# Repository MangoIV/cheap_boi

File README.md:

# The cheap_boi mechanical keyboard
### The cheap_boi is going to be a new custom mechanical keyboard with a low pricetag
## TL;DR
- WIP, PCB v0.2 has been tested and confirmed working 
- cheap, ortholinear keyboard with  OLED-Display and RGB underglow
- Gerbers added, print on own risk
- [BOM](http://htmlpreview.github.io/?https://github.com/MangoIV/cheap_boi/bom/ibom.html)
## Render of front side

## Features
### implemented
- microcontroller ATmega32u4
- ortholinear layout similar to the planck
- 4 individual function keys 
- underglow LEDs using WS2812B
- OLED display using SSD1306
- FR4 Bottom- and Switchplate with windows to see microcontroller and OLED
- have a look at the folder "renders" to see renders of the PCB and plates
- a working firmware exists on my fork of the qmk_firmware on the branch cheap_boi
- acrylic case has been made and is confirmed working 
- easier crystal footprint since v0.2
### planned
- alps/mx hybrid switch cutouts on the top plate
- add some nice silkscreen art on PCB and top plate 
### in the future
- change the design to arm, won't come that quickly though 
### current status concerning prototype
- PCBs and parts have arrived and been tested
- the second Prototype has been built and is fully working 
### problems of the current design
- the fit of the acrylic top plate wit the oled is very tight. this results in the need of filing of some materials off the corner of the oleds, this isn't much work tho and doesn't change the functionality of the oled

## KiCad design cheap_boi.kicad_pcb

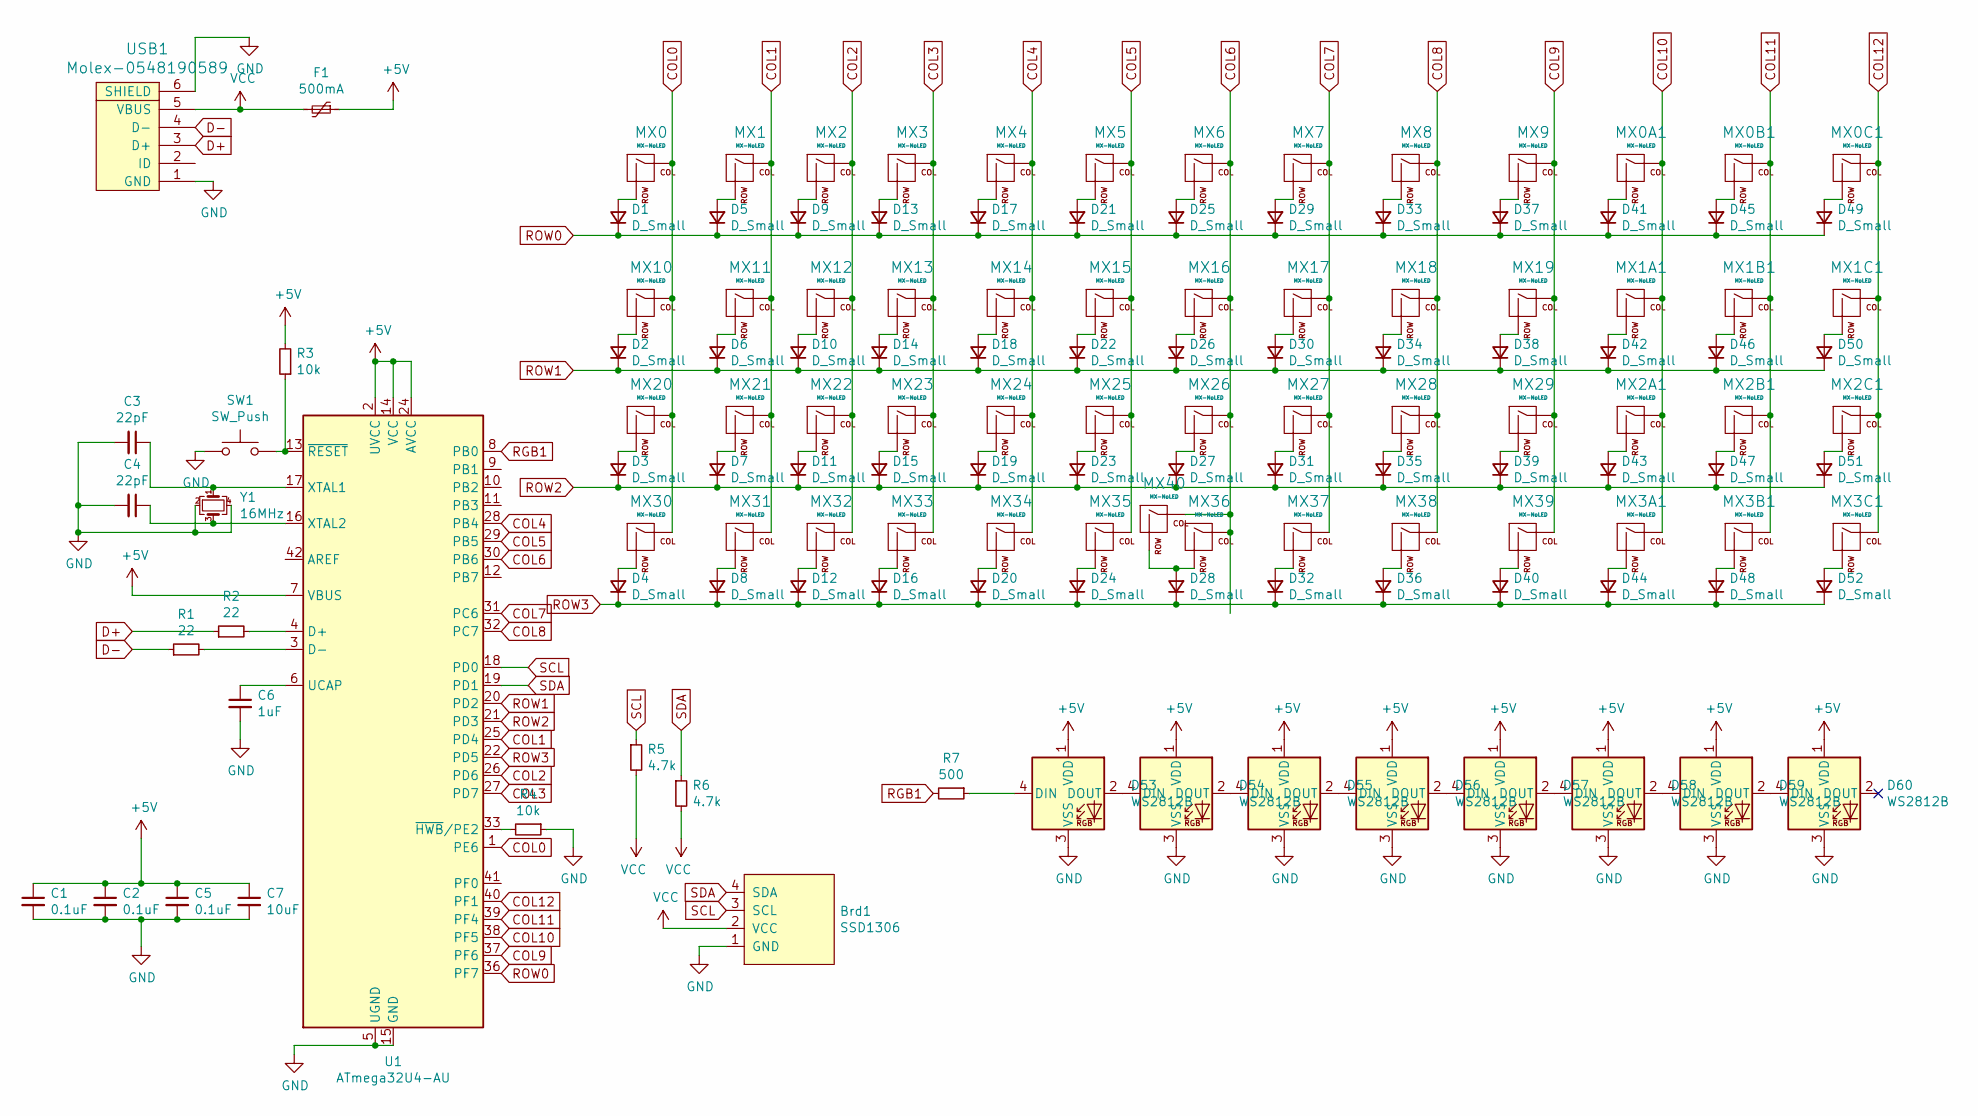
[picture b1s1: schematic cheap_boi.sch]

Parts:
Brd1: SSD1306; 128x64OLED
C1, C2, C5: 0.1uF; C_0805_2012Metric
C3, C4: 22pF; C_0805_2012Metric
C6: 1uF; C_0805_2012Metric
C7: 10uF; C_0805_2012Metric
D1, D2, D3, D4, D5, D6, D7, D8, D9, D10, D11, D12, D13, D14, D15, D16, D17, D18, D19, D20, D21, D22, D23, D24, D25, D26, D27, D28, D29, D30, D31, D32, D33, D34, D35, D36, D37, D38, D39, D40, D41, D42, D43, D44, D45, D46, D47, D48, D49, D50, D51, D52: D_Small; D_SOD-123
D53, D54, D55, D56, D57, D58, D59, D60: WS2812B; LED_WS2812B_PLCC4_5.0x5.0mm_P3.2mm
F1: 500mA; Fuse_1206_3216Metric
MX0, MX0A1, MX0B1, MX0C1, MX1, MX1A1, MX1B1, MX1C1, MX2, MX2A1, MX2B1, MX2C1, MX3, MX3A1, MX3B1, MX3C1, MX4, MX5, MX6, MX7, MX8, MX9, MX10, MX11, MX12, MX13, MX14, MX15, MX16, MX17, MX18, MX19, MX20, MX21, MX22, MX23, MX24, MX25, MX26, MX27, MX28, MX29, MX30, MX31, MX32, MX33, MX34, MX35, MX36, MX37, MX38, MX39: MX-NoLED; MX-1U-NoLED
MX40: MX-NoLED; MX-2U-ReversedStabilizers-NoLED
R1, R2: 22; R_0805_2012Metric
R3, R4: 10k; R_0805_2012Metric
R5, R6: 4.7k; R_0805_2012Metric
R7: 500; R_0805_2012Metric
SW1: SW_Push; SKQG-1155865
U1: ATmega32U4-AU; TQFP-44_10x10mm_P0.8mm
USB1: Molex-0548190589
Y1: 16MHz; Crystal_SMD_3225-4Pin_3.2x2.5mm_HandSoldering

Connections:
+5V: C1.1, C2.1, C5.1, C7.1, D53.1 (VDD), D54.1 (VDD), D55.1 (VDD), D56.1 (VDD), D57.1 (VDD), D58.1 (VDD), D59.1 (VDD), D60.1 (VDD), F1.1, R3.2, U1.2 (UVCC), U1.7 (VBUS), U1.14 (VCC), U1.24 (AVCC), U1.34 (VCC), U1.44 (AVCC)
COL0: MX0.1 (COL), MX10.1 (COL), MX20.1 (COL), MX30.1 (COL), U1.1 (PE6)
COL1: MX1.1 (COL), MX11.1 (COL), MX21.1 (COL), MX31.1 (COL), U1.25 (PD4)
COL2: MX2.1 (COL), MX12.1 (COL), MX22.1 (COL), MX32.1 (COL), U1.26 (PD6)
COL3: MX3.1 (COL), MX13.1 (COL), MX23.1 (COL), MX33.1 (COL), U1.27 (PD7)
COL4: MX4.1 (COL), MX14.1 (COL), MX24.1 (COL), MX34.1 (COL), U1.28 (PB4)
COL5: MX5.1 (COL), MX15.1 (COL), MX25.1 (COL), MX35.1 (COL), U1.29 (PB5)
COL6: MX6.1 (COL), MX16.1 (COL), MX26.1 (COL), MX36.1 (COL), MX40.1 (COL), U1.30 (PB6)
COL7: MX7.1 (COL), MX17.1 (COL), MX27.1 (COL), MX37.1 (COL), U1.31 (PC6)
COL8: MX8.1 (COL), MX18.1 (COL), MX28.1 (COL), MX38.1 (COL), U1.32 (PC7)
COL9: MX9.1 (COL), MX19.1 (COL), MX29.1 (COL), MX39.1 (COL), U1.37 (PF6)
COL10: MX0A1.1 (COL), MX1A1.1 (COL), MX2A1.1 (COL), MX3A1.1 (COL), U1.38 (PF5)
COL11: MX0B1.1 (COL), MX1B1.1 (COL), MX2B1.1 (COL), MX3B1.1 (COL), U1.39 (PF4)
COL12: MX0C1.1 (COL), MX1C1.1 (COL), MX2C1.1 (COL), MX3C1.1 (COL), U1.40 (PF1)
D+: R2.1, USB1.3 (D+)
D-: R1.1, USB1.4 (D-)
GND: Brd1.1 (GND), C1.2, C2.2, C3.2, C4.2, C5.2, C6.2, C7.2, D53.3 (VSS), D54.3 (VSS), D55.3 (VSS), D56.3 (VSS), D57.3 (VSS), D58.3 (VSS), D59.3 (VSS), D60.3 (VSS), R4.1, SW1.1, U1.5 (UGND), U1.15 (GND), U1.23 (GND), U1.35 (GND), U1.43 (GND), USB1.1 (GND), USB1.6 (SHIELD), Y1.2, Y1.4
unnamed: C3.1, U1.17 (XTAL1), Y1.1
unnamed: C4.1, U1.16 (XTAL2), Y1.3
unnamed: C6.1, U1.6 (UCAP)
unnamed: D1.2 (A), MX0.2 (ROW)
unnamed: D2.2 (A), MX10.2 (ROW)
unnamed: D3.2 (A), MX20.2 (ROW)
unnamed: D4.2 (A), MX30.2 (ROW)
unnamed: D5.2 (A), MX1.2 (ROW)
unnamed: D6.2 (A), MX11.2 (ROW)
unnamed: D7.2 (A), MX21.2 (ROW)
unnamed: D8.2 (A), MX31.2 (ROW)
unnamed: D9.2 (A), MX2.2 (ROW)
unnamed: D10.2 (A), MX12.2 (ROW)
unnamed: D11.2 (A), MX22.2 (ROW)
unnamed: D12.2 (A), MX32.2 (ROW)
unnamed: D13.2 (A), MX3.2 (ROW)
unnamed: D14.2 (A), MX13.2 (ROW)
unnamed: D15.2 (A), MX23.2 (ROW)
unnamed: D16.2 (A), MX33.2 (ROW)
unnamed: D17.2 (A), MX4.2 (ROW)
unnamed: D18.2 (A), MX14.2 (ROW)
unnamed: D19.2 (A), MX24.2 (ROW)
unnamed: D20.2 (A), MX34.2 (ROW)
unnamed: D21.2 (A), MX5.2 (ROW)
unnamed: D22.2 (A), MX15.2 (ROW)
unnamed: D23.2 (A), MX25.2 (ROW)
unnamed: D24.2 (A), MX35.2 (ROW)
unnamed: D25.2 (A), MX6.2 (ROW)
unnamed: D26.2 (A), MX16.2 (ROW)
unnamed: D27.2 (A), MX26.2 (ROW)
unnamed: D28.2 (A), MX36.2 (ROW), MX40.2 (ROW)
unnamed: D29.2 (A), MX7.2 (ROW)
unnamed: D30.2 (A), MX17.2 (ROW)
unnamed: D31.2 (A), MX27.2 (ROW)
unnamed: D32.2 (A), MX37.2 (ROW)
unnamed: D33.2 (A), MX8.2 (ROW)
unnamed: D34.2 (A), MX18.2 (ROW)
unnamed: D35.2 (A), MX28.2 (ROW)
unnamed: D36.2 (A), MX38.2 (ROW)
unnamed: D37.2 (A), MX9.2 (ROW)
unnamed: D38.2 (A), MX19.2 (ROW)
unnamed: D39.2 (A), MX29.2 (ROW)
unnamed: D40.2 (A), MX39.2 (ROW)
unnamed: D41.2 (A), MX0A1.2 (ROW)
unnamed: D42.2 (A), MX1A1.2 (ROW)
unnamed: D43.2 (A), MX2A1.2 (ROW)
unnamed: D44.2 (A), MX3A1.2 (ROW)
unnamed: D45.2 (A), MX0B1.2 (ROW)
unnamed: D46.2 (A), MX1B1.2 (ROW)
unnamed: D47.2 (A), MX2B1.2 (ROW)
unnamed: D48.2 (A), MX3B1.2 (ROW)
unnamed: D49.2 (A), MX0C1.2 (ROW)
unnamed: D50.2 (A), MX1C1.2 (ROW)
unnamed: D51.2 (A), MX2C1.2 (ROW)
unnamed: D52.2 (A), MX3C1.2 (ROW)
unnamed: D53.2 (DOUT), D54.4 (DIN)
unnamed: D53.4 (DIN), R7.1
unnamed: D54.2 (DOUT), D55.4 (DIN)
unnamed: D55.2 (DOUT), D56.4 (DIN)
unnamed: D56.2 (DOUT), D57.4 (DIN)
unnamed: D57.2 (DOUT), D58.4 (DIN)
unnamed: D58.2 (DOUT), D59.4 (DIN)
unnamed: D59.2 (DOUT), D60.4 (DIN)
unnamed: R1.2, U1.3 (D-)
unnamed: R2.2, U1.4 (D+)
unnamed: R3.1, SW1.2, U1.13 (~RESET)
unnamed: R4.2, U1.33 (~HWB~/PE2)
RGB1: R7.2, U1.8 (PB0)
ROW0: D1.1 (K), D5.1 (K), D9.1 (K), D13.1 (K), D17.1 (K), D21.1 (K), D25.1 (K), D29.1 (K), D33.1 (K), D37.1 (K), D41.1 (K), D45.1 (K), D49.1 (K), U1.36 (PF7)
ROW1: D2.1 (K), D6.1 (K), D10.1 (K), D14.1 (K), D18.1 (K), D22.1 (K), D26.1 (K), D30.1 (K), D34.1 (K), D38.1 (K), D42.1 (K), D46.1 (K), D50.1 (K), U1.20 (PD2)
ROW2: D3.1 (K), D7.1 (K), D11.1 (K), D15.1 (K), D19.1 (K), D23.1 (K), D27.1 (K), D31.1 (K), D35.1 (K), D39.1 (K), D43.1 (K), D47.1 (K), D51.1 (K), U1.21 (PD3)
ROW3: D4.1 (K), D8.1 (K), D12.1 (K), D16.1 (K), D20.1 (K), D24.1 (K), D28.1 (K), D32.1 (K), D36.1 (K), D40.1 (K), D44.1 (K), D48.1 (K), D52.1 (K), U1.22 (PD5)
SCL: Brd1.3 (SCL), R5.1, U1.18 (PD0)
SDA: Brd1.4 (SDA), R6.1, U1.19 (PD1)
VCC: Brd1.2 (VCC), F1.2, R5.2, R6.2, USB1.5 (VBUS)

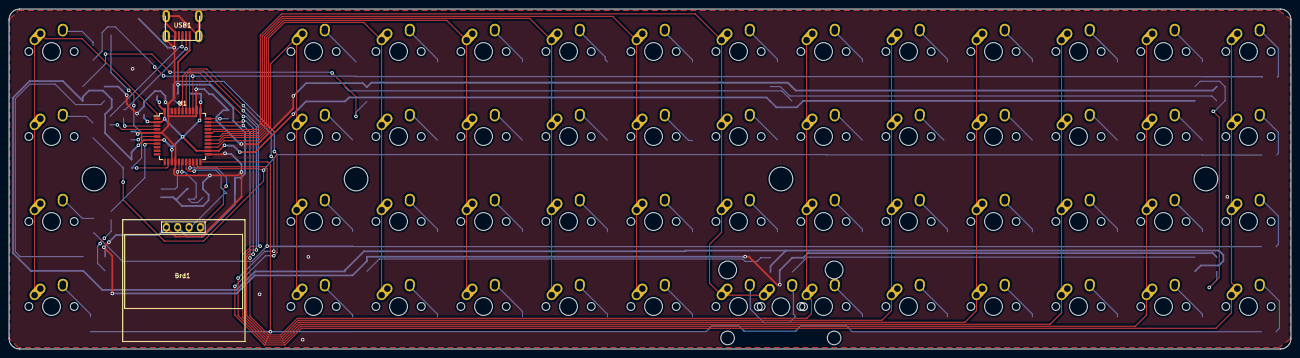
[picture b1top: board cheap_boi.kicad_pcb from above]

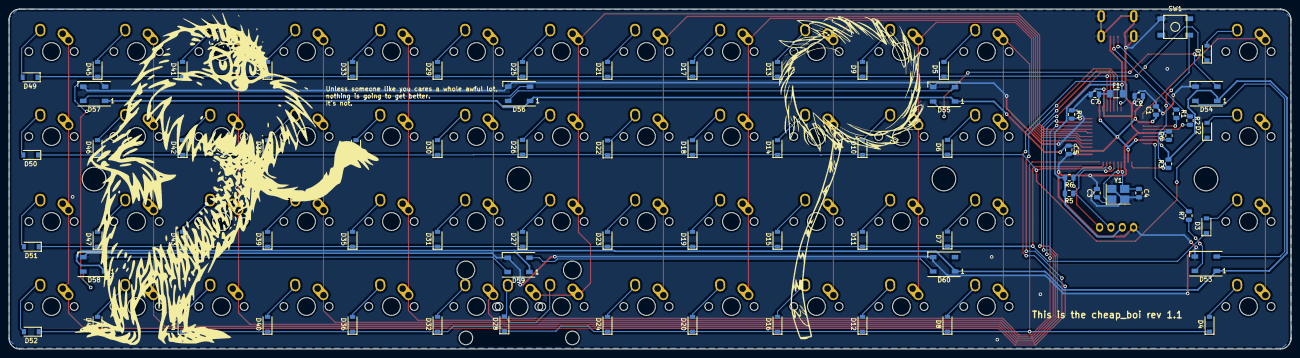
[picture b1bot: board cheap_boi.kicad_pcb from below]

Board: 2 copper layers, 287.3 x 76.2 mm, 137 parts (77 on the bottom side), 92 nets.

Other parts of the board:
 : MountingHole_5.3mm_M5
 #2,  #3,  #4: MountingHole_5.3mm_M5

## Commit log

2020-06-20 create kicad project
2020-06-20 add submodules
2020-06-20 update footprints
2020-06-20 added schematic
2020-06-20 assigned footprints for all components
2020-06-20 sorted and ordered most of the components
2020-06-20 everything added besides cutout and usb-connector
2020-06-20 last commit of the day
2020-06-21 add SSD1306-128x64 submodule
2020-06-21 added RGB breakout and ordered parts in symmetrically
2020-06-21 added connection of rows and cols to microcontroller
2020-06-21 tracing is done, PCB should be functional
2020-06-22 silkscreen text, GND fill, error checking
2020-06-22 added RGB underglow, removed 3 pin breakout for RGB underglow
2020-06-22 add png render front side of pcb
2020-06-22 change file name, merge
2020-06-22 u see what i did
2020-06-22 added evenly distributed groundfill
2020-06-22 revised traces that where 90deg and smaller
2020-06-22 added bom, changed readme
2020-06-22 add Gerbers + gerber zip
2020-06-22 imagine a good commit message, don't have time
2020-06-22 added switch plate
2020-06-22 finished plate, added renders of plate
2020-06-23 bottom plate finished, render added
2020-06-24 added new gerbers
2020-06-24 added step, time to render
2020-06-24 changed folders
2020-06-24 clean up
2020-06-30 changed render plate front
2020-06-30 change render name
2020-07-10 added pics
2020-10-01 we are now on rev 1.1, pcbs soon to be tested
2020-10-01 added shots of the pcb renderer in kicad
2020-10-12 updated the plate to work with 2u and stabs
2020-11-18 Add ibom and link to readme
